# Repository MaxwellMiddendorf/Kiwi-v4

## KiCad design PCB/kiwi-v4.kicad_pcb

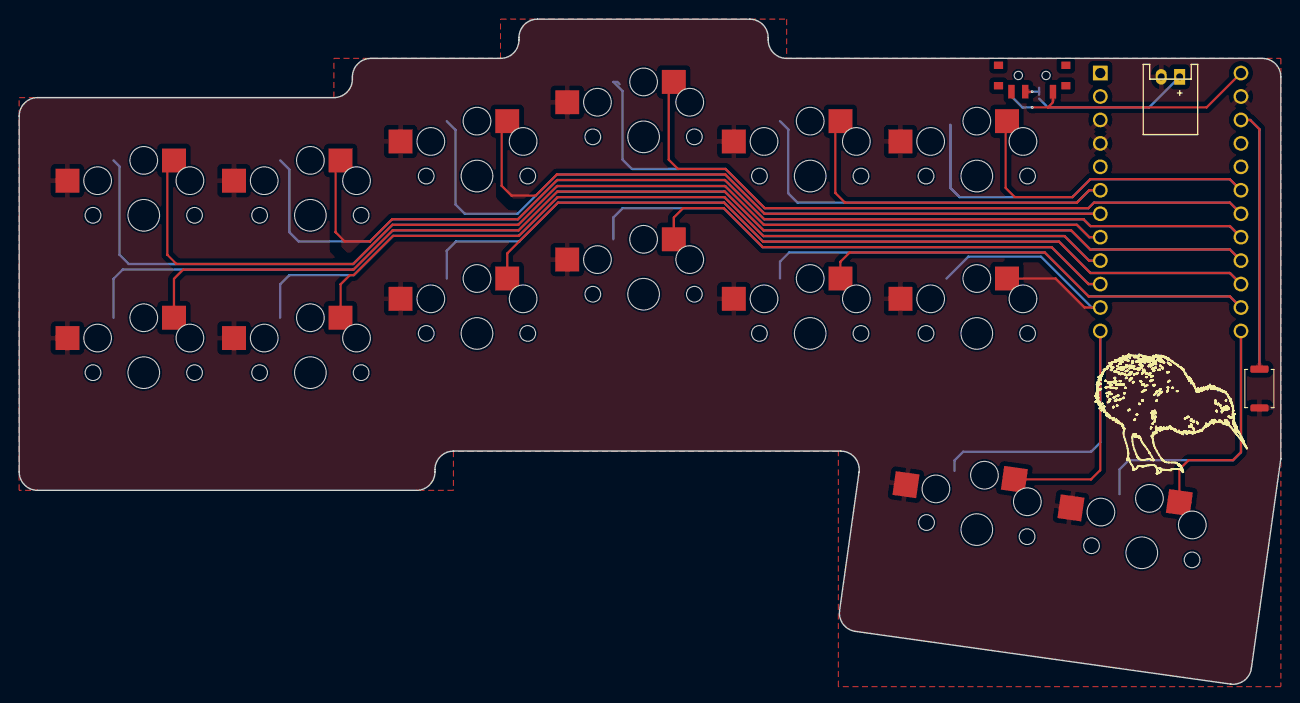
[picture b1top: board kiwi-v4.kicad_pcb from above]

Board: 2 copper layers, 136.7 x 72.1 mm, 18 parts (1 on the bottom side), 18 nets.

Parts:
BT1: Battery_Cell; JST_PH_S2B-PH-K_02x2.00mm_Angled
SW1, SW2, SW3, SW4, SW5, SW6, SW7, SW8, SW9, SW10, SW11, SW12, SW13, SW14: SW_Push; PG1350_Reversible
SW16: SW_SPDT_312; PCM12
SW_15: SW_Push; SW_Push_SPST_NO_Alps_SKRK
U1: ProMicro; ProMicro-NoSilk

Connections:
/BATTERY: SW16.1 (A), U1.24 (RAW)
/R1C1: SW1.1, U1.8 (C6)
/R1C2: SW2.1, U1.17 (F7)
/R1C3: SW3.1, U1.7 (D4)
/R1C4: SW4.1, U1.18 (F6)
/R1C5: SW5.1, U1.6 (SCL)
/R1C6: SW6.1, U1.19 (F5)
/R2C1: SW7.1, U1.16 (B1)
/R2C2: SW8.1, U1.9 (D7)
/R2C3: SW9.1, U1.15 (B3)
/R2C4: SW10.1, U1.10 (E6)
/R2C5: SW11.1, U1.14 (B2)
/R2C6: SW12.1, U1.11 (B4)
/R3C5: SW13.1, U1.12 (B5)
/R3C6: SW14.1, U1.13 (B6)
/RESET: SW_15.1, U1.22 (RST)
GND: BT1.2 (-), SW1.2, SW2.2, SW3.2, SW4.2, SW5.2, SW6.2, SW7.2, SW8.2, SW9.2, SW10.2, SW11.2, SW12.2, SW13.2, SW14.2, SW_15.2, U1.3 (GND), U1.4 (GND), U1.23 (GND)
unnamed: BT1.1 (+), SW16.2 (B)

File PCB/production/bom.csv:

Designator,Footprint,Quantity,Value,LCSC Part #
BT1,JST_PH_S2B-PH-K_02x2.00mm_Angled,1,Battery_Cell,
"SW1, SW10, SW11, SW12, SW13, SW14, SW2, SW3, SW4, SW5, SW6, SW7, SW8, SW9",PG1350_Reversible,14,SW_Push,
SW16,PCM12,1,SW_SPDT_312,
SW_15,SW_Push_SPST_NO_Alps_SKRK,1,SW_Push,
U1,ProMicro-NoSilk,1,ProMicro,

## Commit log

2024-04-19 init commit
2024-04-19 Removed Backups
2024-04-19 removed temp files
2024-04-19 began importing zmk as submodule
2024-04-20 updated remote name
2024-04-20 fixed name
2024-04-20 updated path to local zmk
2024-04-20 fixed url
2024-04-20 fixed path for workflow
2024-04-20 moved path for workflow
2024-04-20 revamped actions
2024-05-01 debug path
2024-05-01 debug path -> changed name
2024-05-01 debug path -> changed branch name
2024-05-01 debug path -> new path
2024-05-01 debug path -> one last shot
2024-05-01 debug: removed west mainfest
2024-05-01 debug: removed parts of west mainfest
2024-05-01 debug: potentially fixed remote
2024-05-01 debug: potentially fixed remote url
2024-05-01 debug: potentially fixed remote url again
2024-05-01 debug: potentially fixed remote url maybe
2024-05-01 debug: potentially fixed remote url maybe for real this time
2024-05-01 debug: zmk version of west local path
2024-05-01 debug: zmk version of west local path in west
2024-05-01 revert
2024-05-19 reverted to orginal building process, and added potential fix to nkro issue
2024-05-19 reversion: moved build file
2024-05-19 reversion: fixed workflow files
2024-05-19 fixed reversed right keymap
2024-05-19 potential nkro fix
2024-05-19 another potential nkro fix
2024-05-19 added experimental configs
2024-05-19 added experimental configs to each side
2024-05-20 enabled console logs
2024-05-20 enabled console logs fixed
2025-01-02 replaced .github folder
